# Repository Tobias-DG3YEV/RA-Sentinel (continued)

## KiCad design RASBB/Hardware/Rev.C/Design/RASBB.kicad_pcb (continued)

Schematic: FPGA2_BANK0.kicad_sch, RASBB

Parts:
C202: 100nF; C_0402_1005Metric; Mfr. Part # 0402B104K500CT; LCSC Part # C152814
C305: 47uF; C_0805_2012Metric; Mfr. Part # GRM21BR61A476ME15L; LCSC Part # C124129
C306: 470nF; C_0402_1005Metric; Mfr. Part # GRM155R71C474KE01D; LCSC Part # C471404
D12: DT2042-04SO-7; SOT95P285X140-6N; Mfr. Part # DT2042-04SO-7; LCSC Part # C2841428
D14, D16: A-SP192YR6C-C01-4T; LED_0603_1608Metric; Mfr. Part # A-SP192YR6C-C01-4T; LCSC Part # C5355433
J15: FPGA2_JTAG; PinHeader_2x03_P1.27mm_Vertical_SMD; Mfr. Part # ZX-PZ1.27-2-3PWZ; LCSC Part # C41370771
R56, R103, R207: 4K7; R_0402_1005Metric; Mfr. Part # WR04X4701FTL; LCSC Part # C163826
R160, R161, R162, R163: 49.9; R_0402_1005Metric; Mfr. Part # RMCF0402FT49R9; LCSC Part # C4229190
R164: 10K; R_0402_1005Metric; Mfr. Part # WR04X1002FTL; LCSC Part # C163810
R206: 1.5K; R_0402_1005Metric; Mfr. Part # WR04X152JTL; LCSC Part # C384376
S3: B3FS-1002P; B3FS-1000P; Mfr. Part # B3FS-1002P; LCSC Part # C271750
U11: XC7A100T-CSG324; BGA324C80P18X18_1500X1500X150; Mfr. Part # XC7A100T-2CSG324I; LCSC Part # C1521791

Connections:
/Audio_IN-OUT/3V3: C202.2, C305.1, C306.1, J15.6 (VCC), R56.1, R103.1, R164.1, R206.1, R207.1, U11.P8 (CFGBVS_0), U11.P12 (M0_0), U11.R9 (VCCO_0); also elsewhere on the board
/FPGA-02/BANK0/FPGA2_DONE: D14.1 (K), R206.2, U11.P10 (DONE_0); also elsewhere on the board
/FPGA-02/BANK0/FPGA2_INIT: D16.1 (K), R207.2, U11.P7 (INIT_B_0)
/FPGA-02/BANK0/FPGA2_TDO: R162.2, U11.E13 (TDO_0)
/FPGA-02/BANK0/JTAG2_TCK: R163.2, U11.E10 (TCK_0)
/FPGA-02/BANK0/JTAG2_TDI: R161.2, U11.E11 (TDI_0)
/FPGA-02/BANK0/JTAG2_TMS: R160.2, U11.E12 (TMS_0)
/FPGA-02/BANK0/TCK_2: D12.6 (I/O4), J15.4 (TCK_2), R163.1
/FPGA-02/BANK0/TDI_2: D12.4 (I/O3), J15.2 (TDI_2), R161.1
/FPGA-02/BANK0/TDO_2: D12.1 (I/O1), J15.3 (TDO_2), R162.1
/FPGA-02/BANK0/TMS_2: D12.3 (I/O2), J15.1 (TMS_2), R160.1
/FPGA-02/FPGA2_PROG: R164.2, S3.3 (B), S3.4 (B), U11.P9 (PROGRAM_B_0); also elsewhere on the board
/SCK_FLASH_FPGA2: U11.E9 (CCLK_0); also elsewhere on the board
GND: C202.1, C305.2, C306.2, D12.2 (VSS), J15.5 (GND), S3.1 (A), S3.2 (A), U11.J9 (VREFN_0), U11.J10 (VP_0), U11.K9 (VN_0), U11.K10 (VREFP_0), U11.L9 (DXN_0), U11.L10 (DXP_0), U11.P11 (M2_0), U11.P13 (M1_0); also elsewhere on the board
unnamed: D14.2 (A), R56.2
unnamed: D16.2 (A), R103.2

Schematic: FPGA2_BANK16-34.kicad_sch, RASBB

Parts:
C307, C311, C312: 4.7uF; C_0402_1005Metric; Mfr. Part # GRM155R61A475KEAAD; LCSC Part # C77004
C308, C313, C314, C315, C316: 470nF; C_0402_1005Metric; Mfr. Part # GRM155R71C474KE01D; LCSC Part # C471404
C310: 100uF; C_1206_3216Metric; Mfr. Part # GRM31CR61A107MEA8L; LCSC Part # C883598
C317: 47nF; C_0402_1005Metric; Mfr. Part # C0402C473J8RAC7867; LCSC Part # C2178375
U11: XC7A100T-CSG324; BGA324C80P18X18_1500X1500X150; Mfr. Part # XC7A100T-2CSG324I; LCSC Part # C1521791

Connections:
/DDR3-01/VCCO_DDR3: C310.1, C311.1, C312.1, C313.1, C314.1, C315.1, C316.1, C317.1, U11.K4 (VCCO_34), U11.N3 (VCCO_34), U11.P6 (VCCO_34), U11.T2 (VCCO_34), U11.U5 (VCCO_34), U11.V8 (VCCO_34); also elsewhere on the board
/DDR3-2/CK_N: U11.V9 (IO_L21N_T3_DQS_34); also elsewhere on the board
/DDR3-2/CK_P: U11.U9 (IO_L21P_T3_DQS_34); also elsewhere on the board
/DDR3-2/DDR301_A0: U11.R2 (IO_L15N_T2_DQS_34); also elsewhere on the board
/DDR3-2/DDR301_A1: U11.M6 (IO_L18P_T2_34); also elsewhere on the board
/DDR3-2/DDR301_A2: U11.N4 (IO_L16N_T2_34); also elsewhere on the board
/DDR3-2/DDR301_A3: U11.T1 (IO_L17N_T2_34); also elsewhere on the board
/DDR3-2/DDR301_A4: U11.N6 (IO_L18N_T2_34); also elsewhere on the board
/DDR3-2/DDR301_A5: U11.R7 (IO_L23P_T3_34); also elsewhere on the board
/DDR3-2/DDR301_A6: U11.V6 (IO_L20N_T3_34); also elsewhere on the board
/DDR3-2/DDR301_A7: U11.U7 (IO_L22P_T3_34); also elsewhere on the board
/DDR3-2/DDR301_A8: U11.R8 (IO_L24P_T3_34); also elsewhere on the board
/DDR3-2/DDR301_A9: U11.V7 (IO_L20P_T3_34); also elsewhere on the board
/DDR3-2/DDR301_A10/AP: U11.R6 (IO_L19P_T3_34); also elsewhere on the board
/DDR3-2/DDR301_A11: U11.U6 (IO_L22N_T3_34); also elsewhere on the board
/DDR3-2/DDR301_A12/nBC: U11.T6 (IO_L23N_T3_34); also elsewhere on the board
/DDR3-2/DDR301_A13: U11.T8 (IO_L24N_T3_34); also elsewhere on the board
/DDR3-2/DDR301_A14: U11.T5 (IO_L12P_T1_MRCC_34); also elsewhere on the board
/DDR3-2/DDR301_BA0: U11.R1 (IO_L17P_T2_34); also elsewhere on the board
/DDR3-2/DDR301_BA1: U11.P4 (IO_L14P_T2_SRCC_34); also elsewhere on the board
/DDR3-2/DDR301_BA2: U11.P2 (IO_L15P_T2_DQS_34); also elsewhere on the board
/DDR3-2/DDR301_CLKE: U11.N5 (IO_L13P_T2_MRCC_34); also elsewhere on the board
/DDR3-2/DDR301_DQ0: U11.K5 (IO_L5P_T0_34); also elsewhere on the board
/DDR3-2/DDR301_DQ1: U11.L3 (IO_L2N_T0_34); also elsewhere on the board
/DDR3-2/DDR301_DQ2: U11.K3 (IO_L2P_T0_34); also elsewhere on the board
/DDR3-2/DDR301_DQ3: U11.L6 (IO_L6P_T0_34); also elsewhere on the board
/DDR3-2/DDR301_DQ4: U11.M3 (IO_L4P_T0_34); also elsewhere on the board
/DDR3-2/DDR301_DQ5: U11.M1 (IO_L1N_T0_34); also elsewhere on the board
/DDR3-2/DDR301_DQ6: U11.L4 (IO_L5N_T0_34); also elsewhere on the board
/DDR3-2/DDR301_DQ7: U11.M2 (IO_L4N_T0_34); also elsewhere on the board
/DDR3-2/DDR301_DQ8: U11.V4 (IO_L10N_T1_34); also elsewhere on the board
/DDR3-2/DDR301_DQ9: U11.T4 (IO_L12N_T1_MRCC_34); also elsewhere on the board
/DDR3-2/DDR301_DQ10: U11.U4 (IO_L8P_T1_34); also elsewhere on the board
/DDR3-2/DDR301_DQ11: U11.V5 (IO_L10P_T1_34); also elsewhere on the board
/DDR3-2/DDR301_DQ12: U11.V1 (IO_L7N_T1_34); also elsewhere on the board
/DDR3-2/DDR301_DQ13: U11.T3 (IO_L11N_T1_SRCC_34); also elsewhere on the board
/DDR3-2/DDR301_DQ14: U11.U3 (IO_L8N_T1_34); also elsewhere on the board
/DDR3-2/DDR301_DQ15: U11.R3 (IO_L11P_T1_SRCC_34); also elsewhere on the board
/DDR3-2/DDR301_LDM: U11.L1 (IO_L1P_T0_34); also elsewhere on the board
/DDR3-2/DDR301_LDQS_N: U11.N1 (IO_L3N_T0_DQS_34); also elsewhere on the board
/DDR3-2/DDR301_LDQS_P: U11.N2 (IO_L3P_T0_DQS_34); also elsewhere on the board
/DDR3-2/DDR301_ODT: U11.R5 (IO_L19N_T3_VREF_34); also elsewhere on the board
/DDR3-2/DDR301_UDM: U11.U1 (IO_L7P_T1_34); also elsewhere on the board
/DDR3-2/DDR301_UDQS_N: U11.V2 (IO_L9N_T1_DQS_34); also elsewhere on the board
/DDR3-2/DDR301_UDQS_P: U11.U2 (IO_L9P_T1_DQS_34); also elsewhere on the board
/DDR3-2/DDR301_nCAS: U11.M4 (IO_L16P_T2_34); also elsewhere on the board
/DDR3-2/DDR301_nCS: U11.U8 (IO_25_34); also elsewhere on the board
/DDR3-2/DDR301_nRAS: U11.P3 (IO_L14N_T2_SRCC_34); also elsewhere on the board
/DDR3-2/DDR301_nRST: U11.K6 (IO_0_34); also elsewhere on the board
/DDR3-2/DDR301_nWE: U11.P5 (IO_L13N_T2_MRCC_34); also elsewhere on the board
/FPGA-01/1V8: C307.1, C308.1, U11.B10 (VCCO_16); also elsewhere on the board
GND: C307.2, C308.2, C310.2, C311.2, C312.2, C313.2, C314.2, C315.2, C316.2, C317.2; also elsewhere on the board

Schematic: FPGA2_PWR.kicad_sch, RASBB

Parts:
C187: 47uF; C_0805_2012Metric; Mfr. Part # GRM21BR61A476ME15L; LCSC Part # C124129
C269, C273, C274, C275, C277, C278, C280, C281, C284, C285, C287, C289, C291, C293: 470nF; C_0402_1005Metric; Mfr. Part # GRM155R71C474KE01D; LCSC Part # C471404
C282, C302, C303, C304: 100uF; C_1206_3216Metric; Mfr. Part # GRM31CR61A107MEA8L; LCSC Part # C883598
C290, C292, C294, C295, C296, C297, C298, C299, C300, C301: 4.7uF; C_0402_1005Metric; Mfr. Part # GRM155R61A475KEAAD; LCSC Part # C77004
U11: XC7A100T-CSG324; BGA324C80P18X18_1500X1500X150; Mfr. Part # XC7A100T-2CSG324I; LCSC Part # C1521791

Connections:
/FPGA-01/1V8: C187.1, C275.1, C280.1, C284.1, C287.1, C290.1, C292.1, C294.1, U11.E8 (VCCBATT_0), U11.F12 (VCCAUX), U11.H10 (VCCADC_0), U11.H12 (VCCAUX), U11.K12 (VCCAUX), U11.M12 (VCCAUX); also elsewhere on the board
/POWER/VSEN_P: C269.1, C273.1, C274.1, C277.1, C278.1, C281.1, C282.1, C285.1, C289.1, C291.1, C293.1, C295.1, C296.1, C297.1, C298.1, C299.1, C300.1, C301.1, C302.1, C303.1, C304.1, U11.F8 (VCCINT), U11.F10 (VCCBRAM), U11.G7 (VCCINT), U11.G9 (VCCINT), U11.G11 (VCCBRAM), U11.H8 (VCCINT), U11.J7 (VCCINT), U11.J11 (VCCINT), U11.K8 (VCCINT), U11.L7 (VCCINT), U11.L11 (VCCINT), U11.M8 (VCCINT), U11.M10 (VCCINT), U11.N7 (VCCINT), U11.N9 (VCCINT), U11.N11 (VCCINT); also elsewhere on the board
GND: C187.2, C269.2, C273.2, C274.2, C275.2, C277.2, C278.2, C280.2, C281.2, C282.2, C284.2, C285.2, C287.2, C289.2, C290.2, C291.2, C292.2, C293.2, C294.2, C295.2, C296.2, C297.2, C298.2, C299.2, C300.2, C301.2, C302.2, C303.2, C304.2, U11.A2 (GND), U11.A12 (GND), U11.B5 (GND), U11.B15 (GND), U11.C8 (GND), U11.C18 (GND), U11.D1 (GND), U11.D11 (GND), U11.E4 (GND), U11.E14 (GND), U11.F7 (GND), U11.F9 (GND), U11.F11 (GND), U11.F17 (GND), U11.G8 (GND), U11.G10 (GND), U11.G12 (GND), U11.H3 (GND), U11.H7 (GND), U11.H9 (GNDADC_0), U11.H11 (GND), U11.H13 (GND), U11.J6 (GND), U11.J8 (GND), U11.J12 (GND), U11.J16 (GND), U11.K7 (GND), U11.K11 (GND), U11.L2 (GND), U11.L8 (GND), U11.L12 (GND), U11.M5 (GND), U11.M7 (GND), U11.M9 (GND), U11.M11 (GND), U11.M15 (GND), U11.N8 (GND), U11.N10 (GND), U11.N12 (GND), U11.N18 (GND), U11.P1 (GND), U11.R4 (GND), U11.R14 (GND), U11.T7 (GND), U11.T17 (GND), U11.U10 (GND), U11.V3 (GND), U11.V13 (GND); also elsewhere on the board

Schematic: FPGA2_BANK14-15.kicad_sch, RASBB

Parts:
C195, C332: 100uF; C_1206_3216Metric; Mfr. Part # GRM31CR61A107MEA8L; LCSC Part # C883598
C326, C327, C328, C329, C335, C336, C337, C338: 470nF; C_0402_1005Metric; Mfr. Part # GRM155R71C474KE01D; LCSC Part # C471404
C330, C331, C333, C334: 4.7uF; C_0402_1005Metric; Mfr. Part # GRM155R61A475KEAAD; LCSC Part # C77004
C339: 47nF; C_0402_1005Metric; Mfr. Part # C0402C473J8RAC7867; LCSC Part # C2178375
D22: A-SP192DGHC-C01-4T; LED_0603_1608Metric; Mfr. Part # A-SP192DGHC-C01-4T; LCSC Part # C19171301
D23: A-SP192GS1D-C01-4T; LED_0603_1608Metric; Mfr. Part # A-SP192GS1D-C01-4T; LCSC Part # C5355434
R146, R147: 1K; R_0402_1005Metric; Mfr. Part # MR04X1001FTL; LCSC Part # C327796
U11: XC7A100T-CSG324; BGA324C80P18X18_1500X1500X150; Mfr. Part # XC7A100T-2CSG324I; LCSC Part # C1521791

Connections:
/Audio_IN-OUT/3V3: C195.1, C326.1, C327.1, C328.1, C329.1, C330.1, C331.1, C332.1, C333.1, C334.1, C335.1, C336.1, C337.1, C338.1, C339.1, U11.A17 (VCCO_15), U11.C13 (VCCO_15), U11.D16 (VCCO_15), U11.G15 (VCCO_15), U11.H18 (VCCO_15), U11.K14 (VCCO_15), U11.L17 (VCCO_14), U11.N13 (VCCO_14), U11.P16 (VCCO_14), U11.T12 (VCCO_14), U11.U15 (VCCO_14), U11.V18 (VCCO_14); also elsewhere on the board
/CLK_OVR_ETH: U11.L16 (IO_L3N_T0_DQS_EMCCLK_14); also elsewhere on the board
/CS2_FLASH_uC: U11.U18 (IO_L17N_T2_A13_D29_14); also elsewhere on the board
/CS_FLASH_FPGA2: U11.L13 (IO_L6P_T0_FCS_B_14); also elsewhere on the board
/DEBUG_A0_F: U11.F15 (IO_L14P_T2_SRCC_15); also elsewhere on the board
/DEBUG_A1_F: U11.H17 (IO_L18P_T2_A24_15); also elsewhere on the board
/DEBUG_A2_F: U11.G18 (IO_L22P_T3_A17_15); also elsewhere on the board
/DEBUG_A3_F: U11.H16 (IO_L13P_T2_MRCC_15); also elsewhere on the board
/DEBUG_A4_F: U11.F16 (IO_L14N_T2_SRCC_15); also elsewhere on the board
/DEBUG_A5_F: U11.H15 (IO_L19N_T3_A21_VREF_15); also elsewhere on the board
/DEBUG_A6_F: U11.E15 (IO_L11P_T1_SRCC_15); also elsewhere on the board
/DEBUG_A7_F: U11.H14 (IO_L15P_T2_DQS_15); also elsewhere on the board
/DEBUG_D0_F: U11.E16 (IO_L11N_T1_SRCC_15); also elsewhere on the board
/DEBUG_D1_F: U11.G13 (IO_0_15); also elsewhere on the board
/DEBUG_D2_F: U11.E18 (IO_L21P_T3_DQS_15); also elsewhere on the board
/DEBUG_D3_F: U11.K16 (IO_25_15); also elsewhere on the board
/DEBUG_D4_F: U11.G17 (IO_L18N_T2_A23_15); also elsewhere on the board
/DEBUG_D5_F: U11.G14 (IO_L15N_T2_DQS_ADV_B_15); also elsewhere on the board
/DEBUG_D6_F: U11.E17 (IO_L16P_T2_A28_15); also elsewhere on the board
/DEBUG_D7_F: U11.G16 (IO_L13N_T2_MRCC_15); also elsewhere on the board
/DEBUG_D8_F: U11.D17 (IO_L16N_T2_A27_15); also elsewhere on the board
/DEBUG_D9_F: U11.A11 (IO_L4N_T0_15); also elsewhere on the board
/DEBUG_D10_F: U11.D15 (IO_L12P_T1_MRCC_15); also elsewhere on the board
/DEBUG_D11_F: U11.B11 (IO_L4P_T0_15); also elsewhere on the board
/DEBUG_D12_F: U11.D14 (IO_L1P_T0_AD0P_15); also elsewhere on the board
/DEBUG_D13_F: U11.C12 (IO_L3P_T0_DQS_AD1P_15); also elsewhere on the board
/DEBUG_D14_F: U11.F18 (IO_L22N_T3_A16_15); also elsewhere on the board
/DEBUG_D15_F: U11.B12 (IO_L3N_T0_DQS_AD1N_15); also elsewhere on the board
/DEBUG_D16_F: U11.D18 (IO_L21N_T3_DQS_A18_15); also elsewhere on the board
/DEBUG_D17_F: U11.A13 (IO_L9P_T1_DQS_AD3P_15); also elsewhere on the board
/DEBUG_D18_F: U11.B18 (IO_L10P_T1_AD11P_15); also elsewhere on the board
/DEBUG_D19_F: U11.D12 (IO_L6P_T0_15); also elsewhere on the board
/DEBUG_D20_F: U11.B17 (IO_L7N_T1_AD2N_15); also elsewhere on the board
/DEBUG_D21_F: U11.B13 (IO_L2P_T0_AD8P_15); also elsewhere on the board
/DEBUG_D22_F: U11.A18 (IO_L10N_T1_AD11N_15); also elsewhere on the board
/DEBUG_D23_F: U11.A14 (IO_L9N_T1_DQS_AD3N_15); also elsewhere on the board
/DEBUG_D24_F: U11.A16 (IO_L8N_T1_AD10N_15); also elsewhere on the board
/DEBUG_D25_F: U11.D13 (IO_L6N_T0_VREF_15); also elsewhere on the board
/DEBUG_D26_F: U11.B16 (IO_L7P_T1_AD2P_15); also elsewhere on the board
/DEBUG_D27_F: U11.B14 (IO_L2N_T0_AD8N_15); also elsewhere on the board
/DEBUG_D28_F: U11.C15 (IO_L12N_T1_MRCC_15); also elsewhere on the board
/DEBUG_D29_F: U11.A15 (IO_L8P_T1_AD10P_15); also elsewhere on the board
/DEBUG_D30_F: U11.C16 (IO_L20P_T3_A20_15); also elsewhere on the board
/DEBUG_D31_F: U11.C14 (IO_L1N_T0_AD0N_15); also elsewhere on the board
/FPGA2_RESET: U11.C17 (IO_L20N_T3_A19_15); also elsewhere on the board
/FPGA-02/F2_B14_P15: U11.P15 (IO_L13P_T2_MRCC_14); also elsewhere on the board
/FPGA-02/F2_B14_R15: U11.R15 (IO_L13N_T2_MRCC_14); also elsewhere on the board
/FPGA-02/F2_B14_R16: U11.R16 (IO_L15P_T2_DQS_RDWR_B_14); also elsewhere on the board
/FPGA-02/F2_B14_T15: U11.T15 (IO_L14N_T2_SRCC_14); also elsewhere on the board
/FPGA-02/F2_B14_T16: U11.T16 (IO_L15N_T2_DQS_DOUT_CSO_B_14); also elsewhere on the board
/FPGA-02/F2_B14_U14: U11.U14 (IO_L22P_T3_A05_D21_14); also elsewhere on the board
/FPGA-02/F2_B14_U16: U11.U16 (IO_L18P_T2_A12_D28_14); also elsewhere on the board
/FPGA-02/F2_B14_V14: U11.V14 (IO_L22N_T3_A04_D20_14); also elsewhere on the board
/FPGA-02/F2_B14_V15: U11.V15 (IO_L16P_T2_CSI_B_14); also elsewhere on the board
/FPGA-02/F2_B14_V16: U11.V16 (IO_L16N_T2_A15_D31_14); also elsewhere on the board
/FPGA-02/F2_B14_V17: U11.V17 (IO_L18N_T2_A11_D27_14); also elsewhere on the board
/SCK_FLASH_uC: U11.L18 (IO_L4P_T0_D04_14); also elsewhere on the board
/SI_FLASH_FPGA2: U11.K17 (IO_L1P_T0_D00_MOSI_14); also elsewhere on the board
/SI_FLASH_uC: U11.J18 (IO_L23N_T3_FWE_B_15); also elsewhere on the board
/SO_FLASH_FPGA2: U11.K18 (IO_L1N_T0_D01_DIN_14); also elsewhere on the board
/SO_FLASH_uC: U11.J17 (IO_L23P_T3_FOE_B_15); also elsewhere on the board
GND: C195.2, C326.2, C327.2, C328.2, C329.2, C330.2, C331.2, C332.2, C333.2, C334.2, C335.2, C336.2, C337.2, C338.2, C339.2, D22.1 (K), D23.1 (K); also elsewhere on the board
unnamed: D22.2 (A), R146.2
unnamed: D23.2 (A), R147.2
unnamed: R147.1, U11.U11 (IO_L19N_T3_A09_D25_VREF_14)
unnamed: R146.1, U11.U12 (IO_L20P_T3_A08_D24_14)

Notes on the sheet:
DEBUG LEDs

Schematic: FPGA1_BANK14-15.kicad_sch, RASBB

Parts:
C188: 47uF; C_0805_2012Metric; Mfr. Part # GRM21BR61A476ME15L; LCSC Part # C124129
C233, C234, C235, C236, C239, C241, C242, C243, C244, C245, C251, C252, C253, C254, C255, C257: 470nF; C_0402_1005Metric; Mfr. Part # GRM155R71C474KE01D; LCSC Part # C471404
C246, C247, C249, C250: 4.7uF; C_0402_1005Metric; Mfr. Part # GRM155R61A475KEAAD; LCSC Part # C77004
C248: 100uF; C_1206_3216Metric; Mfr. Part # GRM31CR61A107MEA8L; LCSC Part # C883598
D24: A-SP192GS1D-C01-4T; LED_0603_1608Metric; Mfr. Part # A-SP192GS1D-C01-4T; LCSC Part # C5355434
D25: A-SP192DGHC-C01-4T; LED_0603_1608Metric; Mfr. Part # A-SP192DGHC-C01-4T; LCSC Part # C19171301
R148, R149: 1K; R_0402_1005Metric; Mfr. Part # MR04X1001FTL; LCSC Part # C327796
U10: XC7A100T-CSG324; BGA324C80P18X18_1500X1500X150; Mfr. Part # XC7A100T-2CSG324I; LCSC Part # C1521791

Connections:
/Audio_IN-OUT/3V3: C188.2, C233.1, C234.1, C235.1, C236.1, C239.1, C241.1, C242.1, C243.1, C244.1, C245.1, C246.1, C247.1, C248.1, C249.1, C250.1, C251.1, C252.1, C253.1, C254.1, C255.1, C257.1, U10.A17 (VCCO_15), U10.C13 (VCCO_15), U10.D16 (VCCO_15), U10.G15 (VCCO_15), U10.H18 (VCCO_15), U10.K14 (VCCO_15), U10.L17 (VCCO_14), U10.N13 (VCCO_14), U10.P16 (VCCO_14), U10.T12 (VCCO_14), U10.U15 (VCCO_14), U10.V18 (VCCO_14); also elsewhere on the board
/CLK_OVR_ETH: U10.G18 (IO_L22P_T3_A17_15); also elsewhere on the board
/CS_FLASH_uC: U10.E18 (IO_L21P_T3_DQS_15); also elsewhere on the board
/Config-SPI FLASH/CS_Flash_FPGA1: U10.L13 (IO_L6P_T0_FCS_B_14); also elsewhere on the board
/DEBUG_A0_F: U10.N17 (IO_L9P_T1_DQS_14); also elsewhere on the board
/DEBUG_A1_F: U10.R15 (IO_L13N_T2_MRCC_14); also elsewhere on the board
/DEBUG_A2_F: U10.P18 (IO_L9N_T1_DQS_D13_14); also elsewhere on the board
/DEBUG_A3_F: U10.R16 (IO_L15P_T2_DQS_RDWR_B_14); also elsewhere on the board
/DEBUG_A4_F: U10.P17 (IO_L12P_T1_MRCC_14); also elsewhere on the board
/DEBUG_A5_F: U10.P15 (IO_L13P_T2_MRCC_14); also elsewhere on the board
/DEBUG_A6_F: U10.R18 (IO_L7P_T1_D09_14); also elsewhere on the board
/DEBUG_A7_F: U10.N14 (IO_L8P_T1_D11_14); also elsewhere on the board
/DEBUG_D0_F: U10.R17 (IO_L12N_T1_MRCC_14); also elsewhere on the board
/DEBUG_D1_F: U10.N16 (IO_L11N_T1_SRCC_14); also elsewhere on the board
/DEBUG_D2_F: U10.T18 (IO_L7N_T1_D10_14); also elsewhere on the board
/DEBUG_D3_F: U10.N15 (IO_L11P_T1_SRCC_14); also elsewhere on the board
/DEBUG_D4_F: U10.U18 (IO_L17N_T2_A13_D29_14); also elsewhere on the board
/DEBUG_D5_F: U10.M16 (IO_L10P_T1_D14_14); also elsewhere on the board
/DEBUG_D6_F: U10.U17 (IO_L17P_T2_A14_D30_14); also elsewhere on the board
/DEBUG_D7_F: U10.M17 (IO_L10N_T1_D15_14); also elsewhere on the board
/DEBUG_D8_F: U10.V17 (IO_L18N_T2_A11_D27_14); also elsewhere on the board
/DEBUG_D9_F: U10.L18 (IO_L4P_T0_D04_14); also elsewhere on the board
/DEBUG_D10_F: U10.U16 (IO_L18P_T2_A12_D28_14); also elsewhere on the board
/DEBUG_D11_F: U10.M18 (IO_L4N_T0_D05_14); also elsewhere on the board
/DEBUG_D12_F: U10.V16 (IO_L16N_T2_A15_D31_14); also elsewhere on the board
/DEBUG_D13_F: U10.M14 (IO_L2N_T0_D03_14); also elsewhere on the board
/DEBUG_D14_F: U10.V15 (IO_L16P_T2_CSI_B_14); also elsewhere on the board
/DEBUG_D15_F: U10.T10 (IO_L24N_T3_A00_D16_14); also elsewhere on the board
/DEBUG_D16_F: U10.U14 (IO_L22P_T3_A05_D21_14); also elsewhere on the board
/DEBUG_D17_F: U10.T11 (IO_L19P_T3_A10_D26_14); also elsewhere on the board
/DEBUG_D18_F: U10.V14 (IO_L22N_T3_A04_D20_14); also elsewhere on the board
/DEBUG_D19_F: U10.R12 (IO_L5P_T0_D06_14); also elsewhere on the board
/DEBUG_D20_F: U10.U13 (IO_L23N_T3_A02_D18_14); also elsewhere on the board
/DEBUG_D21_F: U10.T13 (IO_L23P_T3_A03_D19_14); also elsewhere on the board
/DEBUG_D22_F: U10.U12 (IO_L20P_T3_A08_D24_14); also elsewhere on the board
/DEBUG_D23_F: U10.R13 (IO_L5N_T0_D07_14); also elsewhere on the board
/DEBUG_D24_F: U10.V10 (IO_L21P_T3_DQS_14); also elsewhere on the board
/DEBUG_D25_F: U10.T14 (IO_L14P_T2_SRCC_14); also elsewhere on the board
/DEBUG_D26_F: U10.V11 (IO_L21N_T3_DQS_A06_D22_14); also elsewhere on the board
/DEBUG_D27_F: U10.P14 (IO_L8N_T1_D12_14); also elsewhere on the board
/DEBUG_D28_F: U10.U11 (IO_L19N_T3_A09_D25_VREF_14); also elsewhere on the board
/DEBUG_D29_F: U10.T15 (IO_L14N_T2_SRCC_14); also elsewhere on the board
/DEBUG_D30_F: U10.V12 (IO_L20N_T3_A07_D23_14); also elsewhere on the board
/DEBUG_D31_F: U10.T16 (IO_L15N_T2_DQS_DOUT_CSO_B_14); also elsewhere on the board
/FPGA1_RESET: U10.F18 (IO_L22N_T3_A16_15); also elsewhere on the board
/FPGA-01/F1_B15_C15: U10.C15 (IO_L12N_T1_MRCC_15); also elsewhere on the board
/FPGA-01/F1_B15_D15: U10.D15 (IO_L12P_T1_MRCC_15); also elsewhere on the board
/FPGA-01/F1_B15_E15: U10.E15 (IO_L11P_T1_SRCC_15); also elsewhere on the board
/FPGA-01/F1_B15_E16: U10.E16 (IO_L11N_T1_SRCC_15); also elsewhere on the board
/FPGA-01/FPGA1_MISO: U10.K18 (IO_L1N_T0_D01_DIN_14); also elsewhere on the board
/FPGA-01/FPGA1_MOSI: U10.K17 (IO_L1P_T0_D00_MOSI_14); also elsewhere on the board
/HDMI/HDMI_CLK_N: U10.A14 (IO_L9N_T1_DQS_AD3N_15); also elsewhere on the board
/HDMI/HDMI_CLK_P: U10.A13 (IO_L9P_T1_DQS_AD3P_15); also elsewhere on the board
/HDMI/HDMI_D0_N: U10.B17 (IO_L7N_T1_AD2N_15); also elsewhere on the board
/HDMI/HDMI_D0_P: U10.B16 (IO_L7P_T1_AD2P_15); also elsewhere on the board
/HDMI/HDMI_D1_N: U10.A16 (IO_L8N_T1_AD10N_15); also elsewhere on the board
/HDMI/HDMI_D1_P: U10.A15 (IO_L8P_T1_AD10P_15); also elsewhere on the board
/HDMI/HDMI_D2_N: U10.A18 (IO_L10N_T1_AD11N_15); also elsewhere on the board
/HDMI/HDMI_D2_P: U10.B18 (IO_L10P_T1_AD11P_15); also elsewhere on the board
/SCK_FLASH_uC: U10.D18 (IO_L21N_T3_DQS_A18_15); also elsewhere on the board
/SI_FLASH_uC: U10.E17 (IO_L16P_T2_A28_15); also elsewhere on the board
/SO_FLASH_uC: U10.D17 (IO_L16N_T2_A27_15); also elsewhere on the board
GND: C188.1, C233.2, C234.2, C235.2, C236.2, C239.2, C241.2, C242.2, C243.2, C244.2, C245.2, C246.2, C247.2, C248.2, C249.2, C250.2, C251.2, C252.2, C253.2, C254.2, C255.2, C257.2, D24.1 (K), D25.1 (K); also elsewhere on the board
unnamed: D24.2 (A), R148.2
unnamed: D25.2 (A), R149.2
unnamed: R148.1, U10.B14 (IO_L2N_T0_AD8N_15)
unnamed: R149.1, U10.B13 (IO_L2P_T0_AD8P_15)

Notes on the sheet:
DEBUG LEDs

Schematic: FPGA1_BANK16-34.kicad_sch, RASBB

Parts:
C75, C224, C229, C230, C231, C232: 470nF; C_0402_1005Metric; Mfr. Part # GRM155R71C474KE01D; LCSC Part # C471404
C223, C227, C228: 4.7uF; C_0402_1005Metric; Mfr. Part # GRM155R61A475KEAAD; LCSC Part # C77004
C226: 100uF; C_1206_3216Metric; Mfr. Part # GRM31CR61A107MEA8L; LCSC Part # C883598
U10: XC7A100T-CSG324; BGA324C80P18X18_1500X1500X150; Mfr. Part # XC7A100T-2CSG324I; LCSC Part # C1521791

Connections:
/DDR3-01/CK_N: U10.V9 (IO_L21N_T3_DQS_34); also elsewhere on the board
/DDR3-01/CK_P: U10.U9 (IO_L21P_T3_DQS_34); also elsewhere on the board
/DDR3-01/DDR301_A0: U10.R2 (IO_L15N_T2_DQS_34); also elsewhere on the board
/DDR3-01/DDR301_A1: U10.M6 (IO_L18P_T2_34); also elsewhere on the board
/DDR3-01/DDR301_A2: U10.N4 (IO_L16N_T2_34); also elsewhere on the board
/DDR3-01/DDR301_A3: U10.T1 (IO_L17N_T2_34); also elsewhere on the board
/DDR3-01/DDR301_A4: U10.N6 (IO_L18N_T2_34); also elsewhere on the board
/DDR3-01/DDR301_A5: U10.R7 (IO_L23P_T3_34); also elsewhere on the board
/DDR3-01/DDR301_A6: U10.V6 (IO_L20N_T3_34); also elsewhere on the board
/DDR3-01/DDR301_A7: U10.U7 (IO_L22P_T3_34); also elsewhere on the board
/DDR3-01/DDR301_A8: U10.R8 (IO_L24P_T3_34); also elsewhere on the board
/DDR3-01/DDR301_A9: U10.V7 (IO_L20P_T3_34); also elsewhere on the board
/DDR3-01/DDR301_A10/AP: U10.R6 (IO_L19P_T3_34); also elsewhere on the board
/DDR3-01/DDR301_A11: U10.U6 (IO_L22N_T3_34); also elsewhere on the board
/DDR3-01/DDR301_A12/nBC: U10.T6 (IO_L23N_T3_34); also elsewhere on the board
/DDR3-01/DDR301_A13: U10.T8 (IO_L24N_T3_34); also elsewhere on the board
/DDR3-01/DDR301_A14: U10.T5 (IO_L12P_T1_MRCC_34); also elsewhere on the board
/DDR3-01/DDR301_BA0: U10.R1 (IO_L17P_T2_34); also elsewhere on the board
/DDR3-01/DDR301_BA1: U10.P4 (IO_L14P_T2_SRCC_34); also elsewhere on the board
/DDR3-01/DDR301_BA2: U10.P2 (IO_L15P_T2_DQS_34); also elsewhere on the board
/DDR3-01/DDR301_CLKE: U10.N5 (IO_L13P_T2_MRCC_34); also elsewhere on the board
/DDR3-01/DDR301_DQ0: U10.K5 (IO_L5P_T0_34); also elsewhere on the board
/DDR3-01/DDR301_DQ1: U10.L3 (IO_L2N_T0_34); also elsewhere on the board
/DDR3-01/DDR301_DQ2: U10.K3 (IO_L2P_T0_34); also elsewhere on the board
/DDR3-01/DDR301_DQ3: U10.L6 (IO_L6P_T0_34); also elsewhere on the board
/DDR3-01/DDR301_DQ4: U10.M3 (IO_L4P_T0_34); also elsewhere on the board
/DDR3-01/DDR301_DQ5: U10.M1 (IO_L1N_T0_34); also elsewhere on the board
/DDR3-01/DDR301_DQ6: U10.L4 (IO_L5N_T0_34); also elsewhere on the board
/DDR3-01/DDR301_DQ7: U10.M2 (IO_L4N_T0_34); also elsewhere on the board
/DDR3-01/DDR301_DQ8: U10.V4 (IO_L10N_T1_34); also elsewhere on the board
/DDR3-01/DDR301_DQ9: U10.T4 (IO_L12N_T1_MRCC_34); also elsewhere on the board
/DDR3-01/DDR301_DQ10: U10.U4 (IO_L8P_T1_34); also elsewhere on the board
/DDR3-01/DDR301_DQ11: U10.V5 (IO_L10P_T1_34); also elsewhere on the board
/DDR3-01/DDR301_DQ12: U10.V1 (IO_L7N_T1_34); also elsewhere on the board
/DDR3-01/DDR301_DQ13: U10.T3 (IO_L11N_T1_SRCC_34); also elsewhere on the board
/DDR3-01/DDR301_DQ14: U10.U3 (IO_L8N_T1_34); also elsewhere on the board
/DDR3-01/DDR301_DQ15: U10.R3 (IO_L11P_T1_SRCC_34); also elsewhere on the board
/DDR3-01/DDR301_LDM: U10.L1 (IO_L1P_T0_34); also elsewhere on the board
/DDR3-01/DDR301_LDQS_N: U10.N1 (IO_L3N_T0_DQS_34); also elsewhere on the board
/DDR3-01/DDR301_LDQS_P: U10.N2 (IO_L3P_T0_DQS_34); also elsewhere on the board
/DDR3-01/DDR301_ODT: U10.R5 (IO_L19N_T3_VREF_34); also elsewhere on the board
/DDR3-01/DDR301_UDM: U10.U1 (IO_L7P_T1_34); also elsewhere on the board
/DDR3-01/DDR301_UDQS_N: U10.V2 (IO_L9N_T1_DQS_34); also elsewhere on the board
/DDR3-01/DDR301_UDQS_P: U10.U2 (IO_L9P_T1_DQS_34); also elsewhere on the board
/DDR3-01/DDR301_nCAS: U10.M4 (IO_L16P_T2_34); also elsewhere on the board
/DDR3-01/DDR301_nCS: U10.U8 (IO_25_34); also elsewhere on the board
/DDR3-01/DDR301_nRAS: U10.P3 (IO_L14N_T2_SRCC_34); also elsewhere on the board
/DDR3-01/DDR301_nRST: U10.K6 (IO_0_34); also elsewhere on the board
/DDR3-01/DDR301_nWE: U10.P5 (IO_L13N_T2_MRCC_34); also elsewhere on the board
/DDR3-01/VCCO_DDR3: C75.1, C226.1, C227.1, C228.1, C229.1, C230.1, C231.1, C232.1, U10.K4 (VCCO_34), U10.N3 (VCCO_34), U10.P6 (VCCO_34), U10.T2 (VCCO_34), U10.U5 (VCCO_34), U10.V8 (VCCO_34); also elsewhere on the board
/FPGA-01/1V8: C223.1, C224.1, U10.B10 (VCCO_16); also elsewhere on the board
GND: C75.2, C223.2, C224.2, C226.2, C227.2, C228.2, C229.2, C230.2, C231.2, C232.2; also elsewhere on the board

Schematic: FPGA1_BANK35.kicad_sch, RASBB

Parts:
C182, C225, C261, C262, C263, C264, C265: 470nF; C_0402_1005Metric; Mfr. Part # GRM155R71C474KE01D; LCSC Part # C471404
C192: 47uF; C_0805_2012Metric; Mfr. Part # GRM21BR61A476ME15L; LCSC Part # C124129
C258: 100nF; C_0402_1005Metric; Mfr. Part # 0402B104K500CT; LCSC Part # C152814
C266, C267: 4.7uF; C_0402_1005Metric; Mfr. Part # GRM155R61A475KEAAD; LCSC Part # C77004
J16: FPGA1_CLK_OUT; PinHeader_1x02_P2.54mm_Vertical; Mfr. Part # PZ254V-11-02P; LCSC Part # C492401
R157, R158, R159: 49.9; R_0402_1005Metric; Mfr. Part # RMCF0402FT49R9; LCSC Part # C4229190
U10: XC7A100T-CSG324; BGA324C80P18X18_1500X1500X150; Mfr. Part # XC7A100T-2CSG324I; LCSC Part # C1521791
X3: OT2EL4C4JI-111OLP-50M; Oscillator_SMD_Abracon_ASE-4Pin_3.2x2.5mm; Mfr. Part # OT2EL4C4JI-111OLP-50M; LCSC Part # C5203552

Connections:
/FPGA-01/1V8: C182.1, C192.2, C225.1, C261.1, C262.1, C263.1, C264.1, C265.1, C266.1, C267.1, R157.2, U10.A7 (VCCO_35), U10.C3 (VCCO_35), U10.D6 (VCCO_35), U10.F2 (VCCO_35), U10.G5 (VCCO_35), U10.J1 (VCCO_35); also elsewhere on the board
/PCIE/RX0_N: U10.J2 (IO_L22N_T3_35); also elsewhere on the board
/PCIE/RX0_P: U10.J3 (IO_L22P_T3_35); also elsewhere on the board
/PCIE/RX1_N: U10.K1 (IO_L23N_T3_35); also elsewhere on the board
/PCIE/RX1_P: U10.K2 (IO_L23P_T3_35); also elsewhere on the board
/PCIE/RX2_N: U10.G3 (IO_L20N_T3_35); also elsewhere on the board
/PCIE/RX2_P: U10.G4 (IO_L20P_T3_35); also elsewhere on the board
/PCIE/RX3_N: U10.G1 (IO_L17N_T2_35); also elsewhere on the board
/PCIE/RX3_P: U10.H1 (IO_L17P_T2_35); also elsewhere on the board
/PCIE/RX4_N: U10.G2 (IO_L15N_T2_DQS_35); also elsewhere on the board
/PCIE/RX4_P: U10.H2 (IO_L15P_T2_DQS_35); also elsewhere on the board
/PCIE/RX5_N: U10.E1 (IO_L18N_T2_35); also elsewhere on the board
/PCIE/RX5_P: U10.F1 (IO_L18P_T2_35); also elsewhere on the board
/PCIE/RX6_N: U10.F3 (IO_L13N_T2_MRCC_35); also elsewhere on the board
/PCIE/RX6_P: U10.F4 (IO_L13P_T2_MRCC_35); also elsewhere on the board
/PCIE/RX7_N: U10.A1 (IO_L9N_T1_DQS_AD7N_35); also elsewhere on the board
/PCIE/RX7_P: U10.B1 (IO_L9P_T1_DQS_AD7P_35); also elsewhere on the board
/PCIE/RX8_N: U10.E5 (IO_L5N_T0_AD13N_35); also elsewhere on the board
/PCIE/RX8_P: U10.E6 (IO_L5P_T0_AD13P_35); also elsewhere on the board
/PCIE/RX9_N: U10.B2 (IO_L10N_T1_AD15N_35); also elsewhere on the board
/PCIE/RX9_P: U10.B3 (IO_L10P_T1_AD15P_35); also elsewhere on the board
/PCIE/RX10_N: U10.C1 (IO_L16N_T2_35); also elsewhere on the board
/PCIE/RX10_P: U10.C2 (IO_L16P_T2_35); also elsewhere on the board
/PCIE/RX11_N: U10.A3 (IO_L8N_T1_AD14N_35); also elsewhere on the board
/PCIE/RX11_P: U10.A4 (IO_L8P_T1_AD14P_35); also elsewhere on the board
/PCIE/RX12_N: U10.D4 (IO_L11N_T1_SRCC_35); also elsewhere on the board
/PCIE/RX12_P: U10.D5 (IO_L11P_T1_SRCC_35); also elsewhere on the board
/PCIE/RX13_N: U10.A5 (IO_L3N_T0_DQS_AD5N_35); also elsewhere on the board
/PCIE/RX13_P: U10.A6 (IO_L3P_T0_DQS_AD5P_35); also elsewhere on the board
/PCIE/RX14_N: U10.B4 (IO_L7N_T1_AD6N_35); also elsewhere on the board
/PCIE/RX14_P: U10.C4 (IO_L7P_T1_AD6P_35); also elsewhere on the board
/PCIE/RX15_N: U10.B6 (IO_L2N_T0_AD12N_35); also elsewhere on the board
/PCIE/RX15_P: U10.B7 (IO_L2P_T0_AD12P_35); also elsewhere on the board
/PCIE/RX16_N: U10.C5 (IO_L1N_T0_AD4N_35); also elsewhere on the board
/PCIE/RX16_P: U10.C6 (IO_L1P_T0_AD4P_35); also elsewhere on the board
GND: C182.2, C192.1, C225.2, C258.2, C261.2, C262.2, C263.2, C264.2, C265.2, C266.2, C267.2, J16.2, X3.2 (GND); also elsewhere on the board
unnamed: J16.1, R159.1
unnamed: R159.2, U10.D3 (IO_L12N_T1_MRCC_35)
unnamed: R158.2, U10.E3 (IO_L12P_T1_MRCC_35)
unnamed: C258.1, R157.1, X3.1 (EN), X3.4 (Vdd)
unnamed: R158.1, X3.3 (OUT)

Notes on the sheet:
Clock Test Output

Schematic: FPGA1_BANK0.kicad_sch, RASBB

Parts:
C204: 100nF; C_0402_1005Metric; Mfr. Part # 0402B104K500CT; LCSC Part # C152814
C221: 47uF; C_0805_2012Metric; Mfr. Part # GRM21BR61A476ME15L; LCSC Part # C124129
C222: 470nF; C_0402_1005Metric; Mfr. Part # GRM155R71C474KE01D; LCSC Part # C471404
D11: DT2042-04SO-7; SOT95P285X140-6N; Mfr. Part # DT2042-04SO-7; LCSC Part # C2841428
D13, D15: A-SP192YR6C-C01-4T; LED_0603_1608Metric; Mfr. Part # A-SP192YR6C-C01-4T; LCSC Part # C5355433
J13: FPGA1_JTAG; PinHeader_2x03_P1.27mm_Vertical_SMD; Mfr. Part # ZX-PZ1.27-2-3PWZ; LCSC Part # C41370771
R5, R54, R204: 4K7; R_0402_1005Metric; Mfr. Part # WR04X4701FTL; LCSC Part # C163826
R152, R153, R154, R155: 49.9; R_0402_1005Metric; Mfr. Part # RMCF0402FT49R9; LCSC Part # C4229190
R156: 10K; R_0402_1005Metric; Mfr. Part # WR04X1002FTL; LCSC Part # C163810
R205: 1.5K; R_0402_1005Metric; Mfr. Part # WR04X152JTL; LCSC Part # C384376
S2: B3FS-1002P; B3FS-1000P; Mfr. Part # B3FS-1002P; LCSC Part # C271750
U10: XC7A100T-CSG324; BGA324C80P18X18_1500X1500X150; Mfr. Part # XC7A100T-2CSG324I; LCSC Part # C1521791

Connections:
/Audio_IN-OUT/3V3: C204.2, C221.1, C222.1, J13.6 (VCC), R5.1, R54.1, R156.1, R204.1, R205.1, U10.P8 (CFGBVS_0), U10.P12 (M0_0), U10.R9 (VCCO_0); also elsewhere on the board
/FPGA-01/BANK0/FPGA1_DONE: D13.1 (K), R205.2, U10.P10 (DONE_0); also elsewhere on the board
/FPGA-01/BANK0/FPGA1_INIT: D15.1 (K), R204.2, U10.P7 (INIT_B_0)
/FPGA-01/BANK0/FPGA1_TDO: R154.2, U10.E13 (TDO_0)
/FPGA-01/BANK0/JTAG1_TCK: R155.2, U10.E10 (TCK_0)
/FPGA-01/BANK0/JTAG1_TDI: R153.2, U10.E11 (TDI_0)
/FPGA-01/BANK0/JTAG1_TMS: R152.2, U10.E12 (TMS_0)
/FPGA-01/BANK0/TCK_1: D11.6 (I/O4), J13.4 (TCK_1), R155.1
/FPGA-01/BANK0/TDI_1: D11.4 (I/O3), J13.2 (TDI_2), R153.1
/FPGA-01/BANK0/TDO_1: D11.1 (I/O1), J13.3 (TDO_3), R154.1
/FPGA-01/BANK0/TMS_1: D11.3 (I/O2), J13.1 (TMS_1), R152.1
/FPGA-01/FPGA1_CLK: U10.E9 (CCLK_0); also elsewhere on the board
/FPGA-01/FPGA1_PROG: R156.2, S2.3 (B), S2.4 (B), U10.P9 (PROGRAM_B_0); also elsewhere on the board
GND: C204.1, C221.2, C222.2, D11.2 (VSS), J13.5 (GND), S2.1 (A), S2.2 (A), U10.J9 (VREFN_0), U10.J10 (VP_0), U10.K9 (VN_0), U10.K10 (VREFP_0), U10.L9 (DXN_0), U10.L10 (DXP_0), U10.P11 (M2_0), U10.P13 (M1_0); also elsewhere on the board
unnamed: D13.2 (A), R5.2
unnamed: D15.2 (A), R54.2

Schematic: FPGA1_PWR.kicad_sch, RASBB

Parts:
C184: 47uF; C_0805_2012Metric; Mfr. Part # GRM21BR61A476ME15L; LCSC Part # C124129
C185, C189, C190, C191, C193, C194, C196, C197, C200, C201, C203, C205, C207, C209: 470nF; C_0402_1005Metric; Mfr. Part # GRM155R71C474KE01D; LCSC Part # C471404
C198, C218, C219, C220: 100uF; C_1206_3216Metric; Mfr. Part # GRM31CR61A107MEA8L; LCSC Part # C883598
C206, C208, C210, C211, C212, C213, C214, C215, C216, C217: 4.7uF; C_0402_1005Metric; Mfr. Part # GRM155R61A475KEAAD; LCSC Part # C77004
U10: XC7A100T-CSG324; BGA324C80P18X18_1500X1500X150; Mfr. Part # XC7A100T-2CSG324I; LCSC Part # C1521791

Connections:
/FPGA-01/1V8: C184.1, C191.1, C196.1, C200.1, C203.1, C206.1, C208.1, C210.1, U10.E8 (VCCBATT_0), U10.F12 (VCCAUX), U10.H10 (VCCADC_0), U10.H12 (VCCAUX), U10.K12 (VCCAUX), U10.M12 (VCCAUX); also elsewhere on the board
/POWER/VSEN_P: C185.1, C189.1, C190.1, C193.1, C194.1, C197.1, C198.1, C201.1, C205.1, C207.1, C209.1, C211.1, C212.1, C213.1, C214.1, C215.1, C216.1, C217.1, C218.1, C219.1, C220.1, U10.F8 (VCCINT), U10.F10 (VCCBRAM), U10.G7 (VCCINT), U10.G9 (VCCINT), U10.G11 (VCCBRAM), U10.H8 (VCCINT), U10.J7 (VCCINT), U10.J11 (VCCINT), U10.K8 (VCCINT), U10.L7 (VCCINT), U10.L11 (VCCINT), U10.M8 (VCCINT), U10.M10 (VCCINT), U10.N7 (VCCINT), U10.N9 (VCCINT), U10.N11 (VCCINT); also elsewhere on the board
GND: C184.2, C185.2, C189.2, C190.2, C191.2, C193.2, C194.2, C196.2, C197.2, C198.2, C200.2, C201.2, C203.2, C205.2, C206.2, C207.2, C208.2, C209.2, C210.2, C211.2, C212.2, C213.2, C214.2, C215.2, C216.2, C217.2, C218.2, C219.2, C220.2, U10.A2 (GND), U10.A12 (GND), U10.B5 (GND), U10.B15 (GND), U10.C8 (GND), U10.C18 (GND), U10.D1 (GND), U10.D11 (GND), U10.E4 (GND), U10.E14 (GND), U10.F7 (GND), U10.F9 (GND), U10.F11 (GND), U10.F17 (GND), U10.G8 (GND), U10.G10 (GND), U10.G12 (GND), U10.H3 (GND), U10.H7 (GND), U10.H9 (GNDADC_0), U10.H11 (GND), U10.H13 (GND), U10.J6 (GND), U10.J8 (GND), U10.J12 (GND), U10.J16 (GND), U10.K7 (GND), U10.K11 (GND), U10.L2 (GND), U10.L8 (GND), U10.L12 (GND), U10.M5 (GND), U10.M7 (GND), U10.M9 (GND), U10.M11 (GND), U10.M15 (GND), U10.N8 (GND), U10.N10 (GND), U10.N12 (GND), U10.N18 (GND), U10.P1 (GND), U10.R4 (GND), U10.R14 (GND), U10.T7 (GND), U10.T17 (GND), U10.U10 (GND), U10.V3 (GND), U10.V13 (GND); also elsewhere on the board

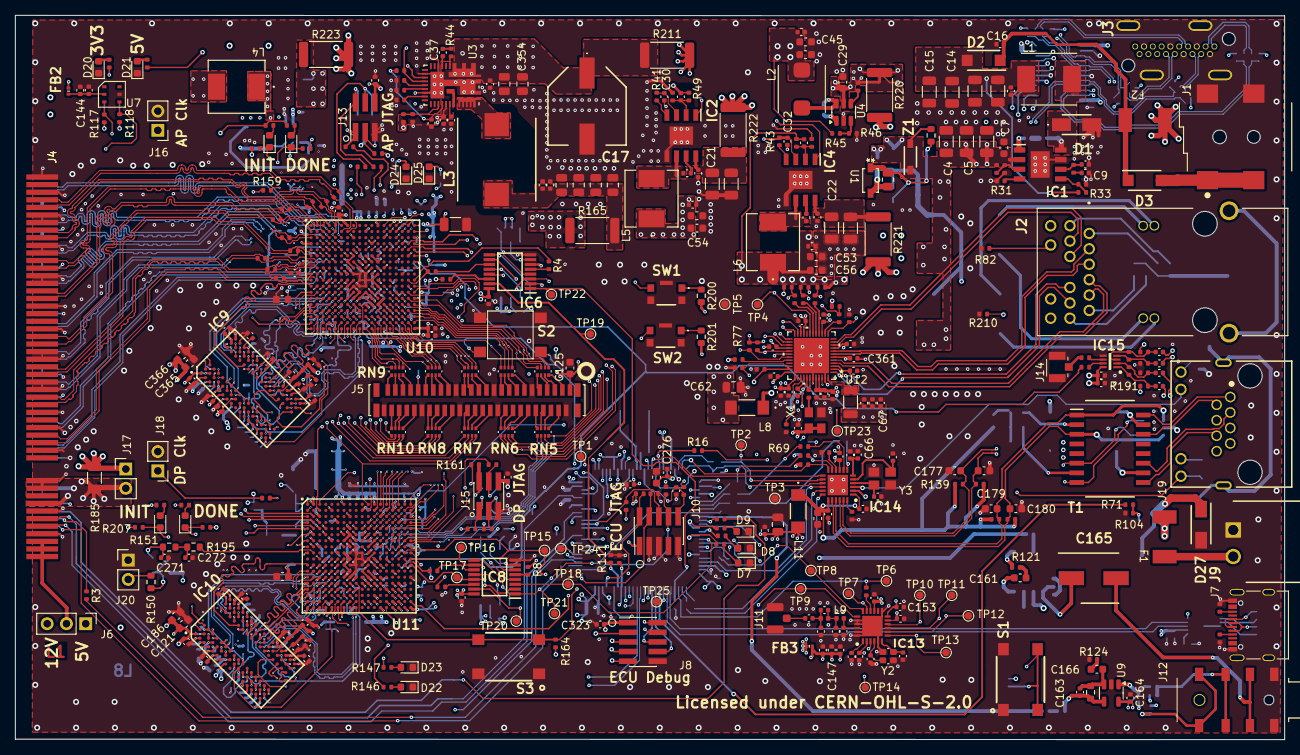
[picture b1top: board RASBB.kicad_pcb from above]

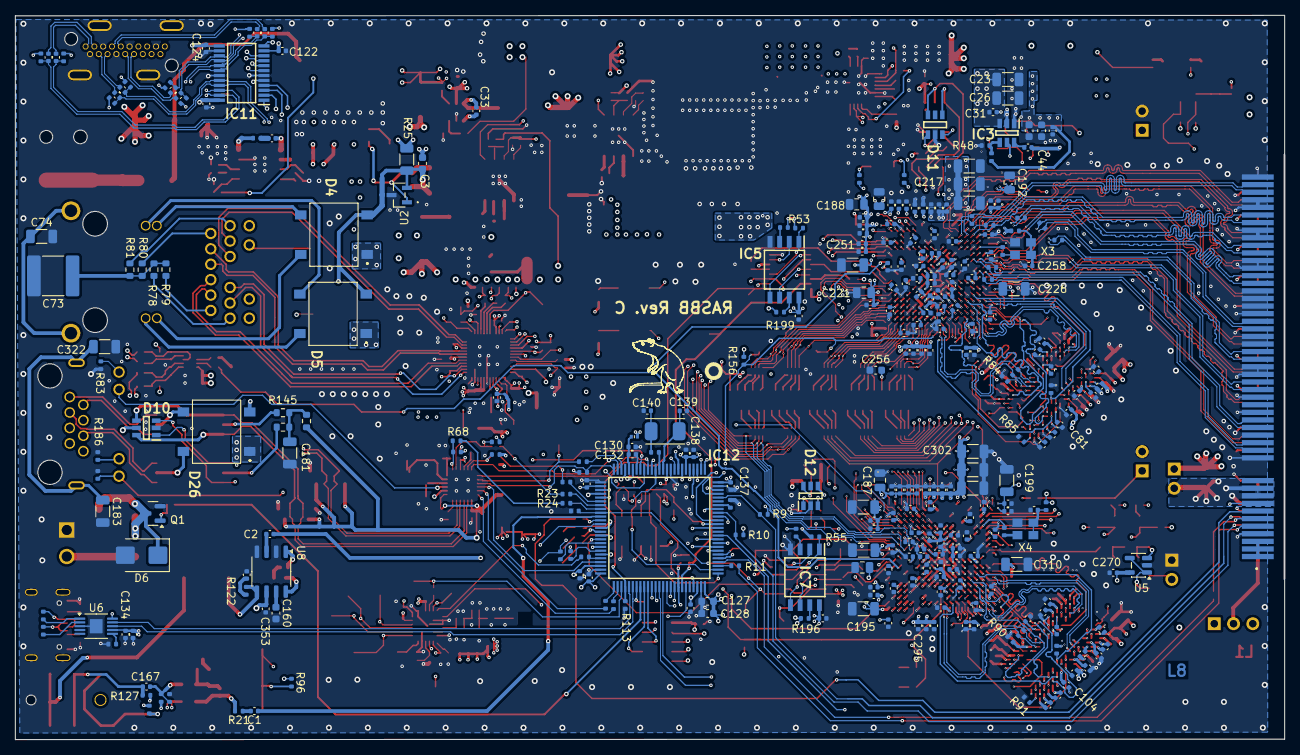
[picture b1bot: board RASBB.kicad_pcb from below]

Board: 8 copper layers, 167.2 x 95.4 mm, 714 parts (312 on the bottom side), 599 nets.
